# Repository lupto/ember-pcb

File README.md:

# EMBER PCB

This is the PCB for interfacing the EMBER macro with FPGA, power supplies, probing, and power measurement.

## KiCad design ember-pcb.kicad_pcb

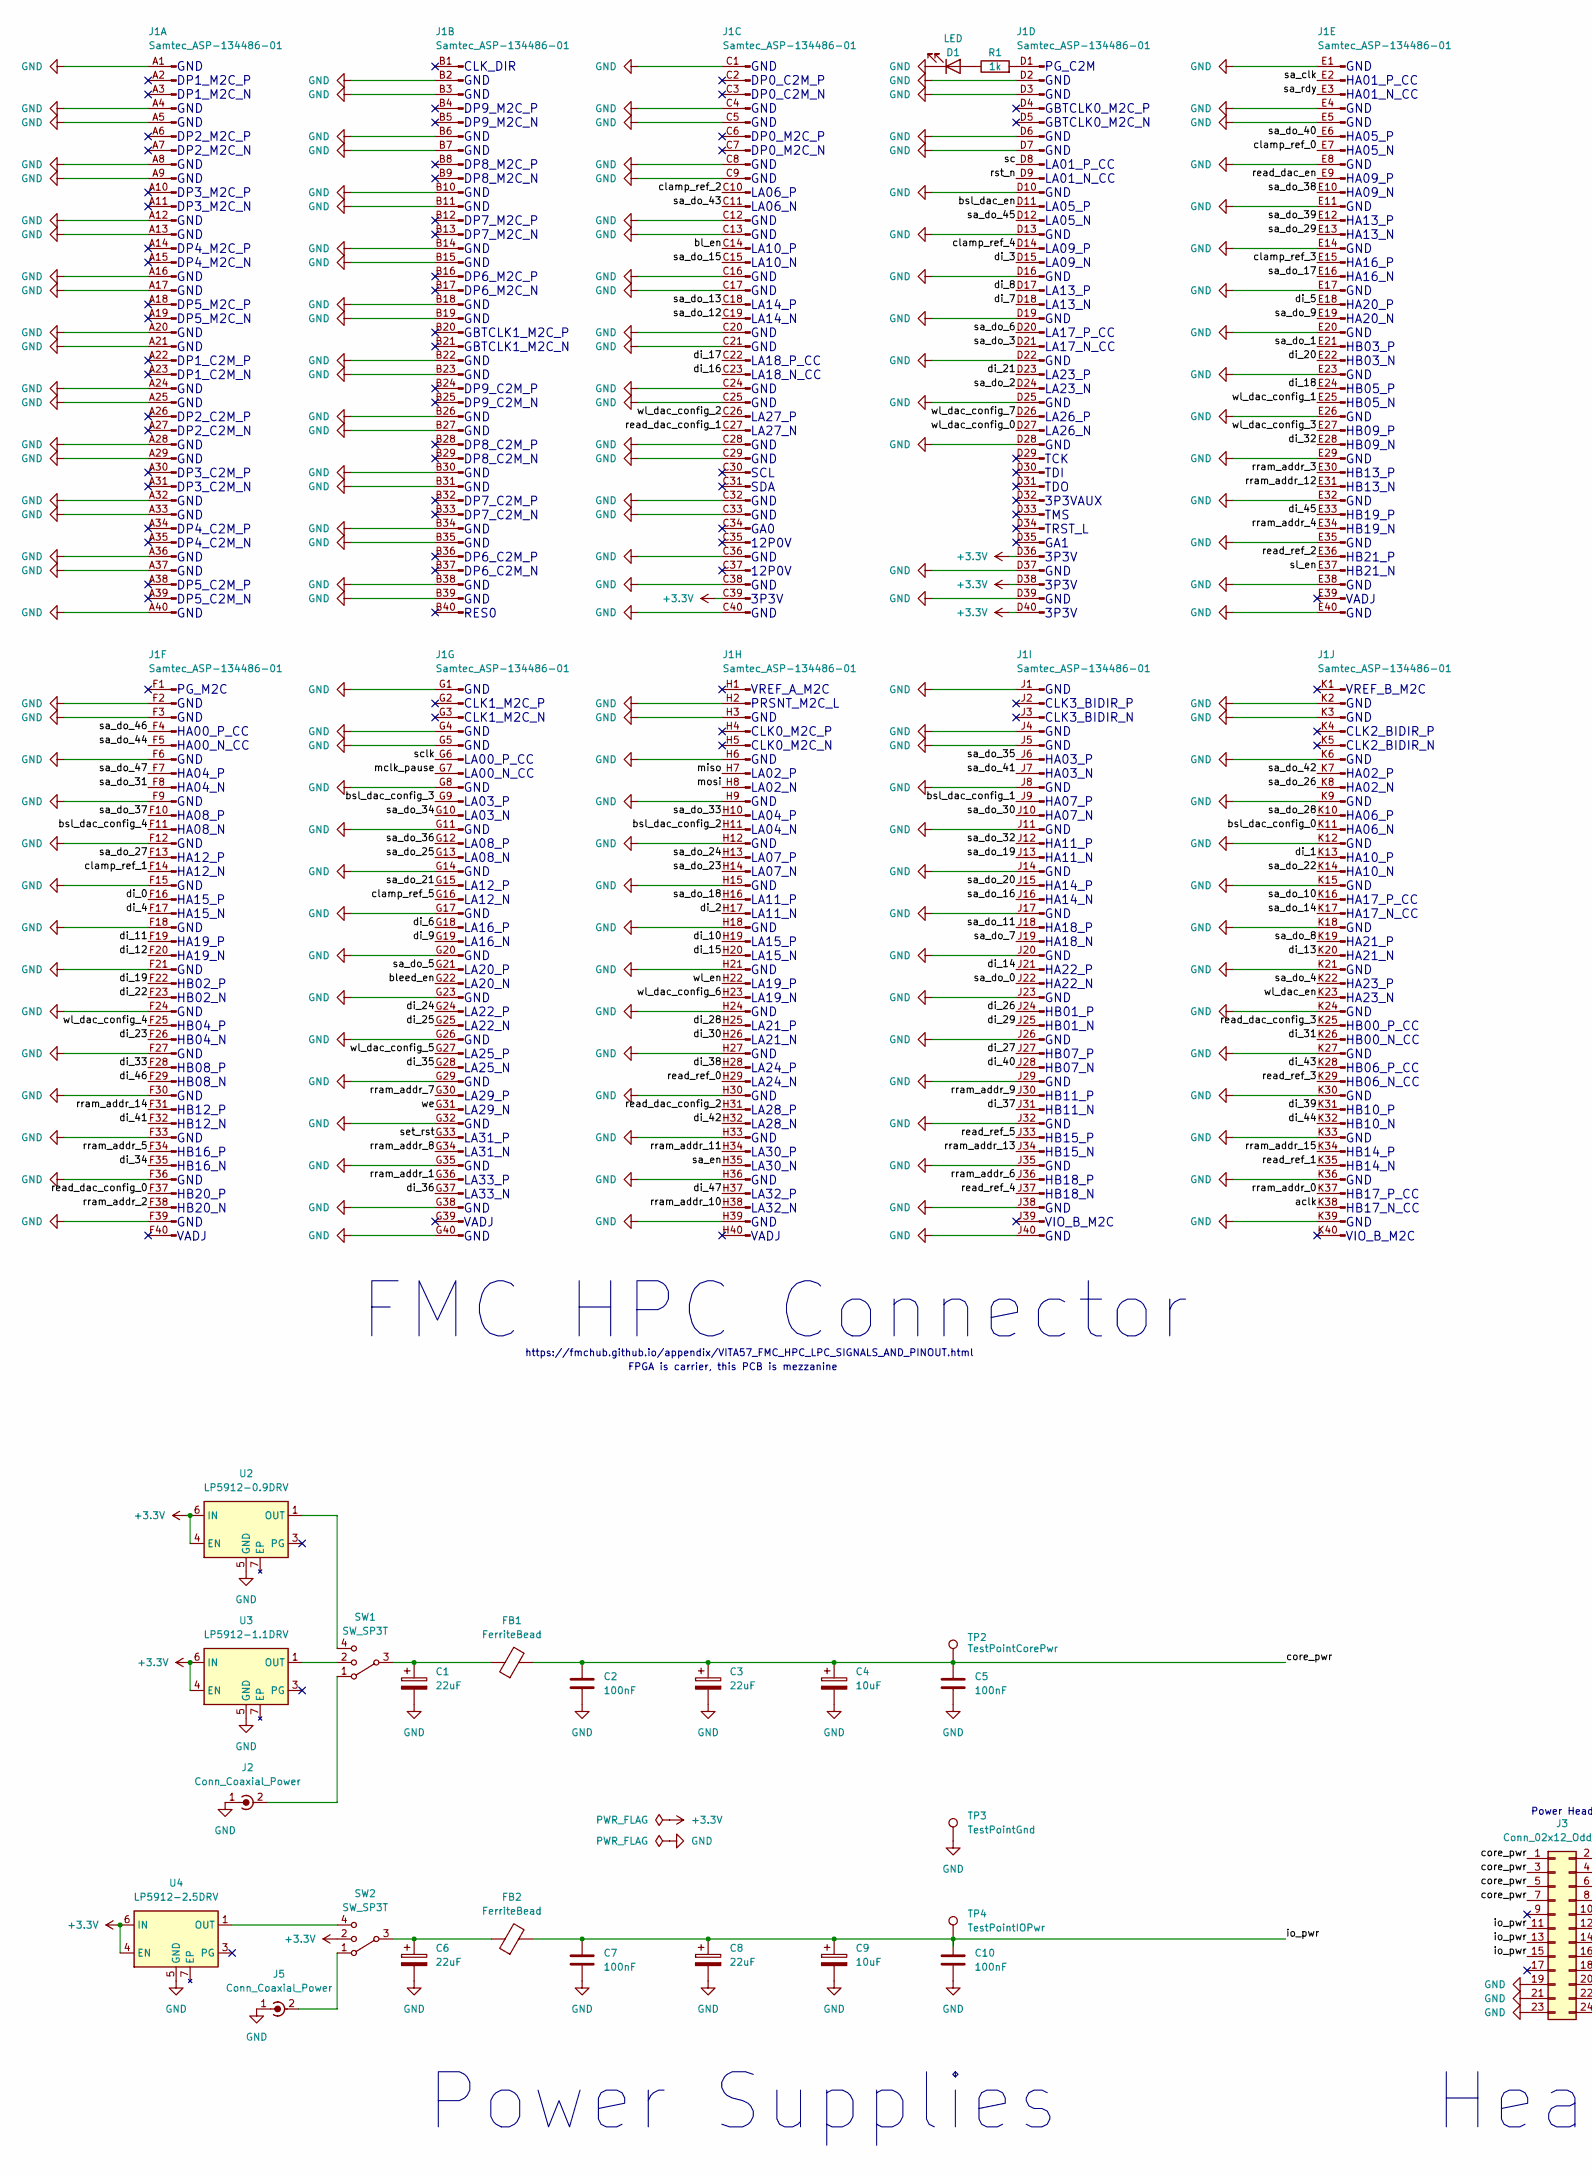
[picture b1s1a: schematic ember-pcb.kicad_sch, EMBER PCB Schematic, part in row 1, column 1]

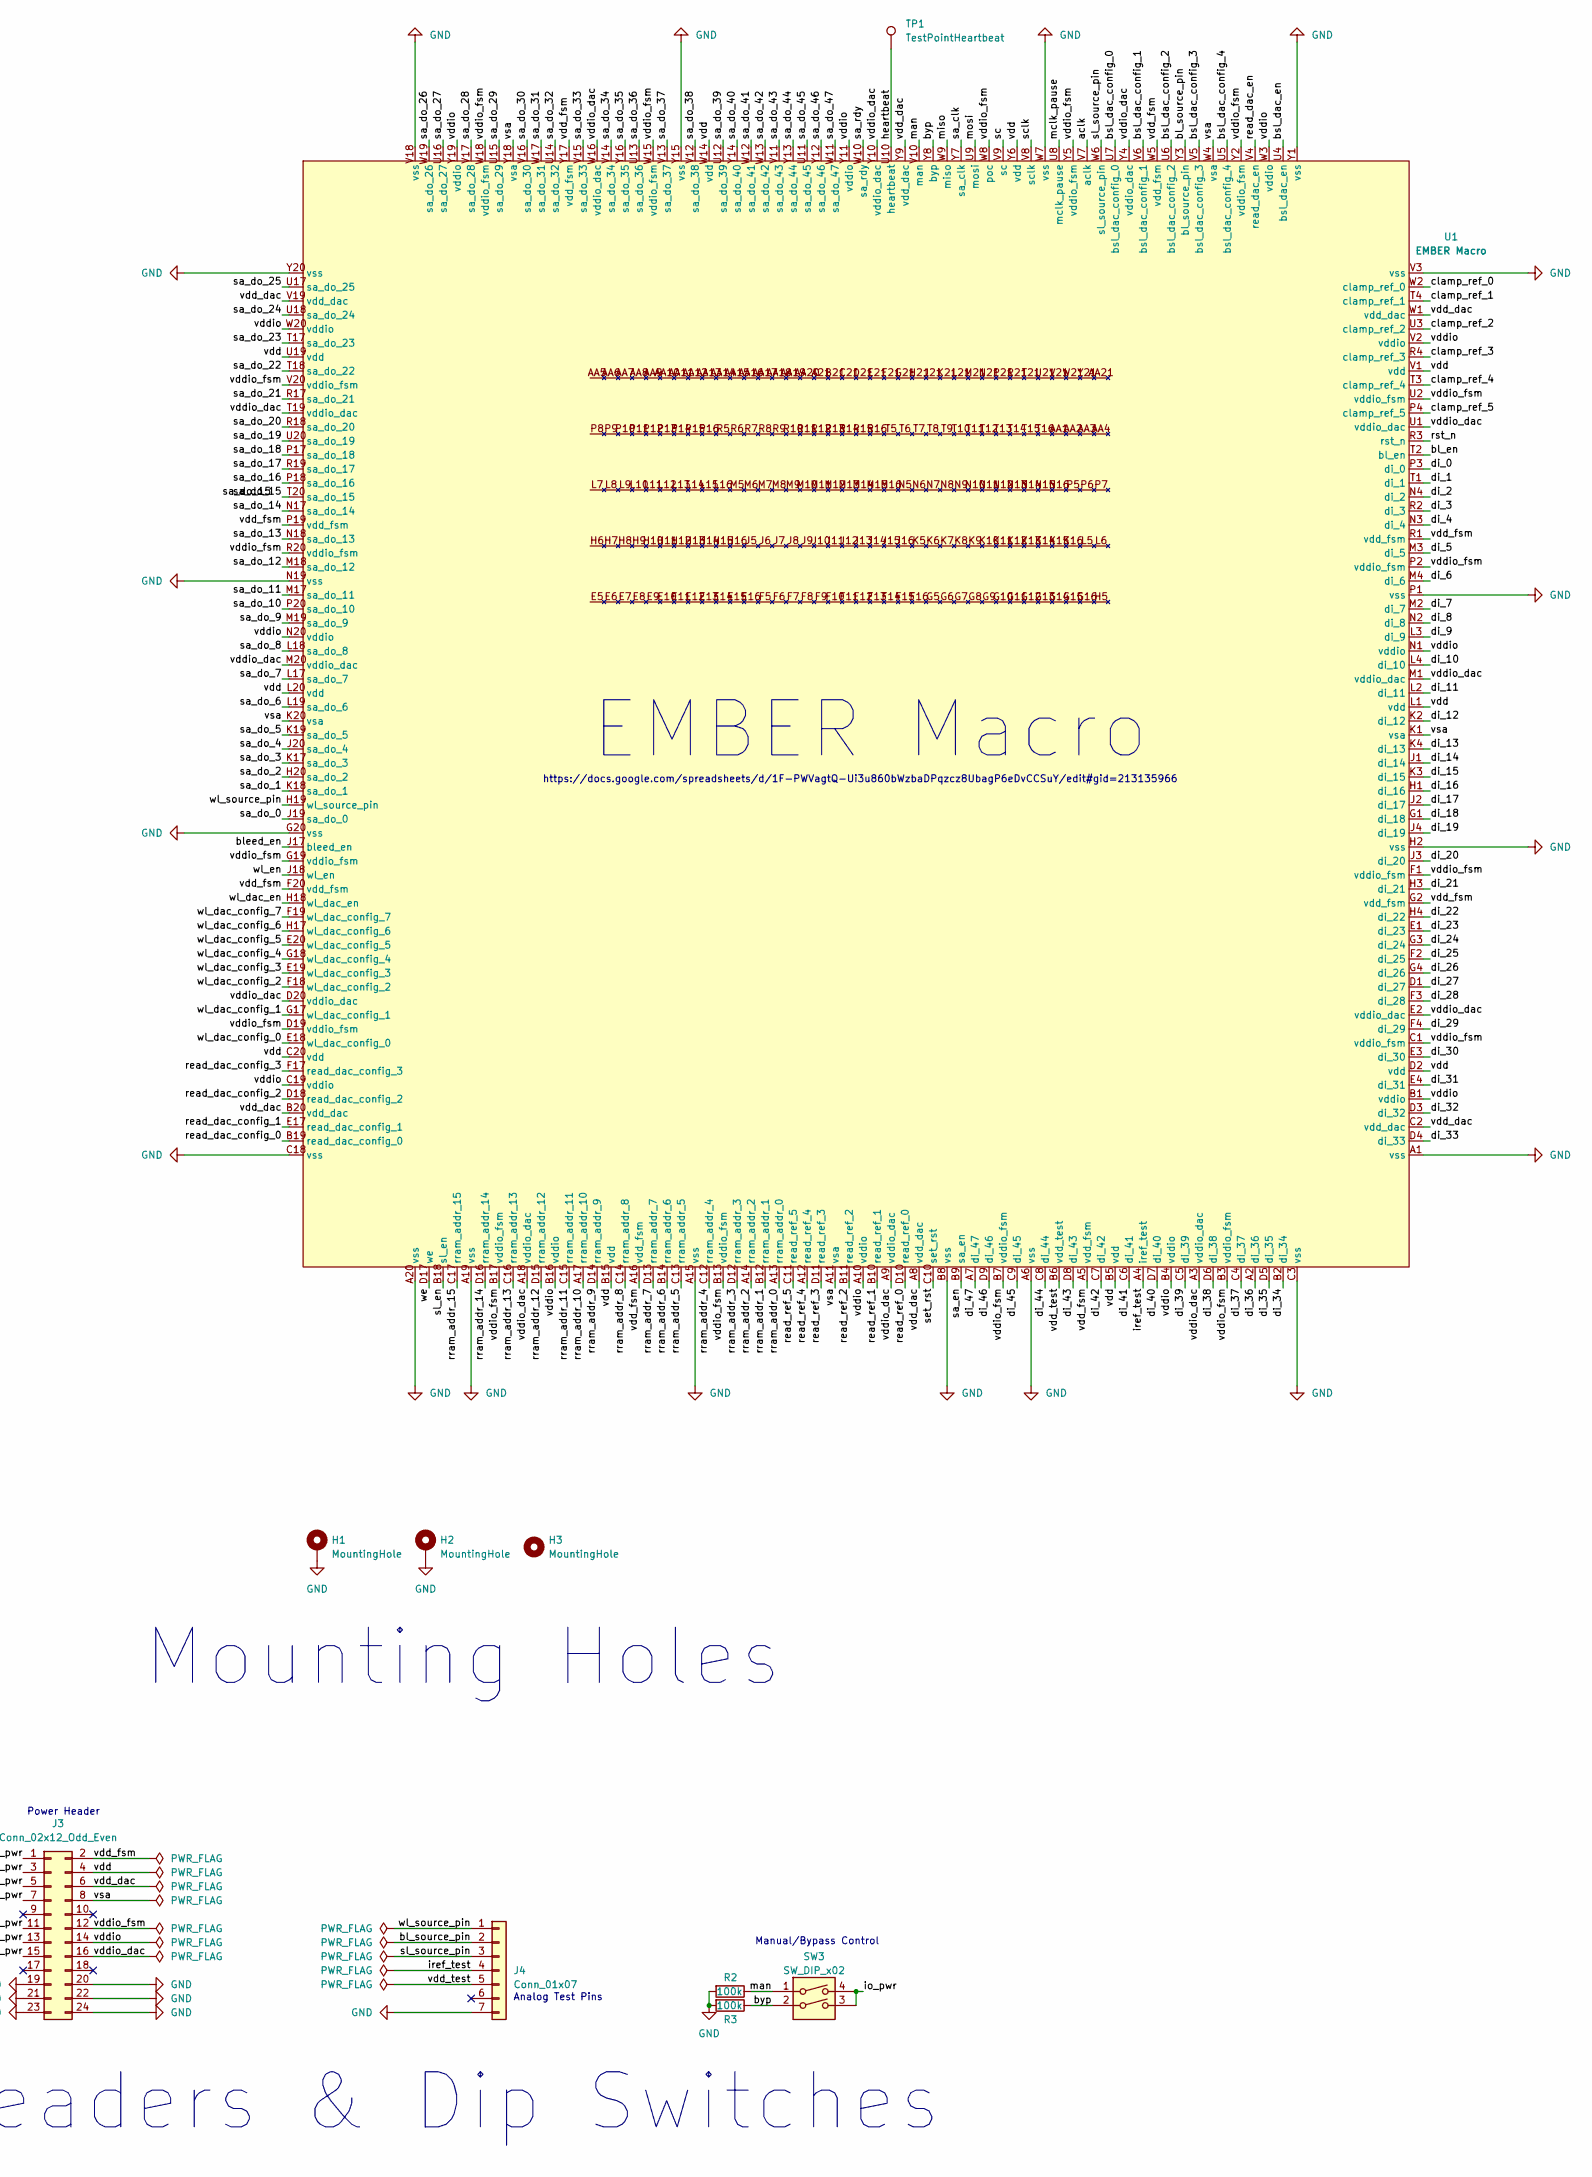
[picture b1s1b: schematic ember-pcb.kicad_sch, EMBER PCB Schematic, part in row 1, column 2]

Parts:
C1, C3, C6, C8: 22uF; CP_Elec_3x5.3
C2, C5, C7, C10: 100nF; CP_Elec_3x5.3
C4, C9: 10uF; CP_Elec_3x5.3
D1: LED; LED_0603_1608Metric
FB1, FB2: FerriteBead; LairdTech_28C0236-0JW-10
H1, H2: MountingHole; MountingHole_2.5mm_Pad
H3: MountingHole; MountingHole_2.5mm
J1: Samtec_ASP-134486-01; Samtec_FMC_ASP-134486-01_10x40_P1.27mm_Vertical
J2, J5: Conn_Coaxial_Power; SMA_Samtec_SMA-J-P-X-ST-EM1_EdgeMount
J3: Conn_02x12_Odd_Even; PinHeader_2x12_P2.54mm_Vertical
J4: Conn_01x07; PinHeader_1x07_P2.54mm_Vertical
R1: 1k; R_0603_1608Metric
R2, R3: 100k; R_0603_1608Metric
SW1, SW2: SW_SP3T; SW_SP3T_PCM13
SW3: SW_DIP_x02; SW_DIP_SPSTx02_Slide_Omron_A6S-210x_W8.9mm_P2.54mm
TP1: TestPointHeartbeat; TestPoint_Pad_D1.0mm
TP2: TestPointCorePwr; TestPoint_Pad_D1.0mm
TP3: TestPointGnd; TestPoint_Pad_D1.0mm
TP4: TestPointIOPwr; TestPoint_Pad_D1.0mm
U1: EMBER Macro; ZIF-441_Aries
U2: LP5912-0.9DRV; WSON-6-1EP_2x2mm_P0.65mm_EP1x1.6mm_ThermalVias
U3: LP5912-1.1DRV; WSON-6-1EP_2x2mm_P0.65mm_EP1x1.6mm_ThermalVias
U4: LP5912-2.5DRV; WSON-6-1EP_2x2mm_P0.65mm_EP1x1.6mm_ThermalVias

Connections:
+3.3V: J1.C39 (Pin_39), J1.D36 (Pin_36), J1.D38 (Pin_38), J1.D40 (Pin_40), SW2.2, U2.4 (EN), U2.6 (IN), U3.4 (EN), U3.6 (IN), U4.4 (EN), U4.6 (IN)
/aclk: J1.K38 (Pin_38), U1.V7 (aclk)
/bl_en: J1.C14 (Pin_14), U1.T2 (bl_en)
/bl_source_pin: J4.2, U1.Y3 (bl_source_pin)
/bleed_en: J1.G22 (Pin_22), U1.J17 (bleed_en)
/bsl_dac_config_0: J1.K11 (Pin_11), U1.U7 (bsl_dac_config_0)
/bsl_dac_config_1: J1.J9 (Pin_9), U1.V6 (bsl_dac_config_1)
/bsl_dac_config_2: J1.H11 (Pin_11), U1.U6 (bsl_dac_config_2)
/bsl_dac_config_3: J1.G9 (Pin_9), U1.V5 (bsl_dac_config_3)
/bsl_dac_config_4: J1.F11 (Pin_11), U1.U5 (bsl_dac_config_4)
/bsl_dac_en: J1.D11 (Pin_11), U1.U4 (bsl_dac_en)
/byp: R3.1, SW3.2, U1.Y8 (byp)
/clamp_ref_0: J1.E7 (Pin_7), U1.W2 (clamp_ref_0)
/clamp_ref_1: J1.F14 (Pin_14), U1.T4 (clamp_ref_1)
/clamp_ref_2: J1.C10 (Pin_10), U1.U3 (clamp_ref_2)
/clamp_ref_3: J1.E15 (Pin_15), U1.R4 (clamp_ref_3)
/clamp_ref_4: J1.D14 (Pin_14), U1.T3 (clamp_ref_4)
/clamp_ref_5: J1.G16 (Pin_16), U1.P4 (clamp_ref_5)
/core_pwr: C2.1, C3.1, C4.1, C5.1, FB1.2, J3.1, J3.3, J3.5, J3.7, TP2.1
/di_0: J1.F16 (Pin_16), U1.P3 (di_0)
/di_1: J1.K13 (Pin_13), U1.T1 (di_1)
/di_2: J1.H17 (Pin_17), U1.N4 (di_2)
/di_3: J1.D15 (Pin_15), U1.R2 (di_3)
/di_4: J1.F17 (Pin_17), U1.N3 (di_4)
/di_5: J1.E18 (Pin_18), U1.M3 (di_5)
/di_6: J1.G18 (Pin_18), U1.M4 (di_6)
/di_7: J1.D18 (Pin_18), U1.M2 (di_7)
/di_8: J1.D17 (Pin_17), U1.N2 (di_8)
/di_9: J1.G19 (Pin_19), U1.L3 (di_9)
/di_10: J1.H19 (Pin_19), U1.L4 (di_10)
/di_11: J1.F19 (Pin_19), U1.L2 (di_11)
/di_12: J1.F20 (Pin_20), U1.K2 (di_12)
/di_13: J1.K20 (Pin_20), U1.K4 (di_13)
/di_14: J1.J21 (Pin_21), U1.J1 (di_14)
/di_15: J1.H20 (Pin_20), U1.K3 (di_15)
/di_16: J1.C23 (Pin_23), U1.H1 (di_16)
/di_17: J1.C22 (Pin_22), U1.J2 (di_17)
/di_18: J1.E24 (Pin_24), U1.G1 (di_18)
/di_19: J1.F22 (Pin_22), U1.J4 (di_19)
/di_20: J1.E22 (Pin_22), U1.J3 (di_20)
/di_21: J1.D23 (Pin_23), U1.H3 (di_21)
/di_22: J1.F23 (Pin_23), U1.H4 (di_22)
/di_23: J1.F26 (Pin_26), U1.E1 (di_23)
/di_24: J1.G24 (Pin_24), U1.G3 (di_24)
/di_25: J1.G25 (Pin_25), U1.F2 (di_25)
/di_26: J1.J24 (Pin_24), U1.G4 (di_26)
/di_27: J1.J27 (Pin_27), U1.D1 (di_27)
/di_28: J1.H25 (Pin_25), U1.F3 (di_28)
/di_29: J1.J25 (Pin_25), U1.F4 (di_29)
/di_30: J1.H26 (Pin_26), U1.E3 (di_30)
/di_31: J1.K26 (Pin_26), U1.E4 (di_31)
/di_32: J1.E28 (Pin_28), U1.D3 (di_32)
/di_33: J1.F28 (Pin_28), U1.D4 (di_33)
/di_34: J1.F35 (Pin_35), U1.B2 (di_34)
/di_35: J1.G28 (Pin_28), U1.D5 (di_35)
/di_36: J1.G37 (Pin_37), U1.A2 (di_36)
/di_37: J1.J31 (Pin_31), U1.C4 (di_37)
/di_38: J1.H28 (Pin_28), U1.D6 (di_38)
/di_39: J1.K31 (Pin_31), U1.C5 (di_39)
/di_40: J1.J28 (Pin_28), U1.D7 (di_40)
/di_41: J1.F32 (Pin_32), U1.C6 (di_41)
/di_42: J1.H32 (Pin_32), U1.C7 (di_42)
/di_43: J1.K28 (Pin_28), U1.D8 (di_43)
/di_44: J1.K32 (Pin_32), U1.C8 (di_44)
/di_45: J1.E33 (Pin_33), U1.C9 (di_45)
/di_46: J1.F29 (Pin_29), U1.D9 (di_46)
/di_47: J1.H37 (Pin_37), U1.A7 (di_47)
/heartbeat: TP1.1, U1.U10 (heartbeat)
/io_pwr: C7.1, C8.1, C9.1, C10.1, FB2.2, J3.11, J3.13, J3.15, SW3.3, SW3.4, TP4.1
/iref_test: J4.4, U1.A4 (iref_test)
/man: R2.1, SW3.1, U1.V10 (man)
/mclk_pause: J1.G7 (Pin_7), U1.U8 (mclk_pause)
/miso: J1.H7 (Pin_7), U1.W9 (miso)
/mosi: J1.H8 (Pin_8), U1.U9 (mosi)
/read_dac_config_0: J1.F37 (Pin_37), U1.B19 (read_dac_config_0)
/read_dac_config_1: J1.C27 (Pin_27), U1.E17 (read_dac_config_1)
/read_dac_config_2: J1.H31 (Pin_31), U1.D18 (read_dac_config_2)
/read_dac_config_3: J1.K25 (Pin_25), U1.F17 (read_dac_config_3)
/read_dac_en: J1.E9 (Pin_9), U1.V4 (read_dac_en)
/read_ref_0: J1.H29 (Pin_29), U1.D10 (read_ref_0)
/read_ref_1: J1.K35 (Pin_35), U1.B10 (read_ref_1)
/read_ref_2: J1.E36 (Pin_36), U1.B11 (read_ref_2)
/read_ref_3: J1.K29 (Pin_29), U1.D11 (read_ref_3)
/read_ref_4: J1.J37 (Pin_37), U1.A12 (read_ref_4)
/read_ref_5: J1.J33 (Pin_33), U1.C11 (read_ref_5)
/rram_addr_0: J1.K37 (Pin_37), U1.A13 (rram_addr_0)
/rram_addr_1: J1.G36 (Pin_36), U1.B12 (rram_addr_1)
/rram_addr_2: J1.F38 (Pin_38), U1.A14 (rram_addr_2)
/rram_addr_3: J1.E30 (Pin_30), U1.D12 (rram_addr_3)
/rram_addr_4: J1.E34 (Pin_34), U1.C12 (rram_addr_4)
/rram_addr_5: J1.F34 (Pin_34), U1.C13 (rram_addr_5)
/rram_addr_6: J1.J36 (Pin_36), U1.B14 (rram_addr_6)
/rram_addr_7: J1.G30 (Pin_30), U1.D13 (rram_addr_7)
/rram_addr_8: J1.G34 (Pin_34), U1.C14 (rram_addr_8)
/rram_addr_9: J1.J30 (Pin_30), U1.D14 (rram_addr_9)
/rram_addr_10: J1.H38 (Pin_38), U1.A17 (rram_addr_10)
/rram_addr_11: J1.H34 (Pin_34), U1.C15 (rram_addr_11)
/rram_addr_12: J1.E31 (Pin_31), U1.D15 (rram_addr_12)
/rram_addr_13: J1.J34 (Pin_34), U1.C16 (rram_addr_13)
/rram_addr_14: J1.F31 (Pin_31), U1.D16 (rram_addr_14)
/rram_addr_15: J1.K34 (Pin_34), U1.C17 (rram_addr_15)
/rst_n: J1.D9 (Pin_9), U1.R3 (rst_n)
/sa_clk: J1.E2 (Pin_2), U1.Y7 (sa_clk)
/sa_do_0: J1.J22 (Pin_22), U1.J19 (sa_do_0)
/sa_do_1: J1.E21 (Pin_21), U1.K18 (sa_do_1)
/sa_do_2: J1.D24 (Pin_24), U1.H20 (sa_do_2)
/sa_do_3: J1.D21 (Pin_21), U1.K17 (sa_do_3)
/sa_do_4: J1.K22 (Pin_22), U1.J20 (sa_do_4)
/sa_do_5: J1.G21 (Pin_21), U1.K19 (sa_do_5)
/sa_do_6: J1.D20 (Pin_20), U1.L19 (sa_do_6)
/sa_do_7: J1.J19 (Pin_19), U1.L17 (sa_do_7)
/sa_do_8: J1.K19 (Pin_19), U1.L18 (sa_do_8)
/sa_do_9: J1.E19 (Pin_19), U1.M19 (sa_do_9)
/sa_do_10: J1.K16 (Pin_16), U1.P20 (sa_do_10)
/sa_do_11: J1.J18 (Pin_18), U1.M17 (sa_do_11)
/sa_do_12: J1.C19 (Pin_19), U1.M18 (sa_do_12)
/sa_do_13: J1.C18 (Pin_18), U1.N18 (sa_do_13)
/sa_do_14: J1.K17 (Pin_17), U1.N17 (sa_do_14)
/sa_do_15: J1.C15 (Pin_15), U1.T20 (sa_do_15)
/sa_do_16: J1.J16 (Pin_16), U1.P18 (sa_do_16)
/sa_do_17: J1.E16 (Pin_16), U1.R19 (sa_do_17)
/sa_do_18: J1.H16 (Pin_16), U1.P17 (sa_do_18)
/sa_do_19: J1.J13 (Pin_13), U1.U20 (sa_do_19)
/sa_do_20: J1.J15 (Pin_15), U1.R18 (sa_do_20)
/sa_do_21: J1.G15 (Pin_15), U1.R17 (sa_do_21)
/sa_do_22: J1.K14 (Pin_14), U1.T18 (sa_do_22)
/sa_do_23: J1.H14 (Pin_14), U1.T17 (sa_do_23)
/sa_do_24: J1.H13 (Pin_13), U1.U18 (sa_do_24)
/sa_do_25: J1.G13 (Pin_13), U1.U17 (sa_do_25)
/sa_do_26: J1.K8 (Pin_8), U1.W19 (sa_do_26)
/sa_do_27: J1.F13 (Pin_13), U1.U16 (sa_do_27)
/sa_do_28: J1.K10 (Pin_10), U1.V17 (sa_do_28)
/sa_do_29: J1.E13 (Pin_13), U1.U15 (sa_do_29)
/sa_do_30: J1.J10 (Pin_10), U1.V16 (sa_do_30)
/sa_do_31: J1.F8 (Pin_8), U1.W17 (sa_do_31)
/sa_do_32: J1.J12 (Pin_12), U1.U14 (sa_do_32)
/sa_do_33: J1.H10 (Pin_10), U1.V15 (sa_do_33)
/sa_do_34: J1.G10 (Pin_10), U1.V14 (sa_do_34)
/sa_do_35: J1.J6 (Pin_6), U1.Y16 (sa_do_35)
/sa_do_36: J1.G12 (Pin_12), U1.U13 (sa_do_36)
/sa_do_37: J1.F10 (Pin_10), U1.V13 (sa_do_37)
/sa_do_38: J1.E10 (Pin_10), U1.V12 (sa_do_38)
/sa_do_39: J1.E12 (Pin_12), U1.U12 (sa_do_39)
/sa_do_40: J1.E6 (Pin_6), U1.Y14 (sa_do_40)
/sa_do_41: J1.J7 (Pin_7), U1.W12 (sa_do_41)
/sa_do_42: J1.K7 (Pin_7), U1.W13 (sa_do_42)
/sa_do_43: J1.C11 (Pin_11), U1.V11 (sa_do_43)
/sa_do_44: J1.F5 (Pin_5), U1.Y13 (sa_do_44)
/sa_do_45: J1.D12 (Pin_12), U1.U11 (sa_do_45)
/sa_do_46: J1.F4 (Pin_4), U1.Y12 (sa_do_46)
/sa_do_47: J1.F7 (Pin_7), U1.W11 (sa_do_47)
/sa_en: J1.H35 (Pin_35), U1.B9 (sa_en)
/sa_rdy: J1.E3 (Pin_3), U1.W10 (sa_rdy)
/sc: J1.D8 (Pin_8), U1.V9 (sc)
/sclk: J1.G6 (Pin_6), U1.V8 (sclk)
/set_rst: J1.G33 (Pin_33), U1.C10 (set_rst)
/sl_en: J1.E37 (Pin_37), U1.B18 (sl_en)
/sl_source_pin: J4.3, U1.W6 (sl_source_pin)
/vdd: J3.4, U1.B5 (vdd), U1.B15 (vdd), U1.C20 (vdd), U1.D2 (vdd), U1.L1 (vdd), U1.L20 (vdd), U1.U19 (vdd), U1.V1 (vdd), U1.W14 (vdd), U1.Y6 (vdd)
/vdd_dac: J3.6, U1.A8 (vdd_dac), U1.B20 (vdd_dac), U1.C2 (vdd_dac), U1.V19 (vdd_dac), U1.W1 (vdd_dac), U1.Y9 (vdd_dac)
/vdd_fsm: J3.2, U1.A5 (vdd_fsm), U1.A16 (vdd_fsm), U1.F20 (vdd_fsm), U1.G2 (vdd_fsm), U1.P19 (vdd_fsm), U1.R1 (vdd_fsm), U1.W5 (vdd_fsm), U1.Y17 (vdd_fsm)
/vdd_test: J4.5, U1.B6 (vdd_test)
/vddio: J3.14, U1.A10 (vddio), U1.B1 (vddio), U1.B4 (vddio), U1.B16 (vddio), U1.C19 (vddio), U1.N1 (vddio), U1.N20 (vddio), U1.V2 (vddio), U1.W3 (vddio), U1.W20 (vddio), U1.Y11 (vddio), U1.Y19 (vddio)
/vddio_dac: J3.16, U1.A3 (vddio_dac), U1.A9 (vddio_dac), U1.A18 (vddio_dac), U1.D20 (vddio_dac), U1.E2 (vddio_dac), U1.M1 (vddio_dac), U1.M20 (vddio_dac), U1.T19 (vddio_dac), U1.U1 (vddio_dac), U1.W16 (vddio_dac), U1.Y4 (vddio_dac), U1.Y10 (vddio_dac)
/vddio_fsm: J3.12, U1.B3 (vddio_fsm), U1.B7 (vddio_fsm), U1.B13 (vddio_fsm), U1.B17 (vddio_fsm), U1.C1 (vddio_fsm), U1.D19 (vddio_fsm), U1.F1 (vddio_fsm), U1.G19 (vddio_fsm), U1.P2 (vddio_fsm), U1.R20 (vddio_fsm), U1.U2 (vddio_fsm), U1.V20 (vddio_fsm), U1.W8 (poc), U1.W15 (vddio_fsm), U1.W18 (vddio_fsm), U1.Y2 (vddio_fsm), U1.Y5 (vddio_fsm)
/vsa: J3.8, U1.A11 (vsa), U1.K1 (vsa), U1.K20 (vsa), U1.W4 (vsa), U1.Y18 (vsa)
/we: J1.G31 (Pin_31), U1.D17 (we)
/wl_dac_config_0: J1.D27 (Pin_27), U1.E18 (wl_dac_config_0)
/wl_dac_config_1: J1.E25 (Pin_25), U1.G17 (wl_dac_config_1)
/wl_dac_config_2: J1.C26 (Pin_26), U1.F18 (wl_dac_config_2)
/wl_dac_config_3: J1.E27 (Pin_27), U1.E19 (wl_dac_config_3)
/wl_dac_config_4: J1.F25 (Pin_25), U1.G18 (wl_dac_config_4)
/wl_dac_config_5: J1.G27 (Pin_27), U1.E20 (wl_dac_config_5)
/wl_dac_config_6: J1.H23 (Pin_23), U1.H17 (wl_dac_config_6)
/wl_dac_config_7: J1.D26 (Pin_26), U1.F19 (wl_dac_config_7)
/wl_dac_en: J1.K23 (Pin_23), U1.H18 (wl_dac_en)
/wl_en: J1.H22 (Pin_22), U1.J18 (wl_en)
/wl_source_pin: J4.1, U1.H19 (wl_source_pin)
GND: C1.2, C2.2, C3.2, C4.2, C5.2, C6.2, C7.2, C8.2, C9.2, C10.2, D1.1 (K), H1.1, H2.1, J1.A1 (Pin_1), J1.A4 (Pin_4), J1.A5 (Pin_5), J1.A8 (Pin_8), J1.A9 (Pin_9), J1.A12 (Pin_12), J1.A13 (Pin_13), J1.A16 (Pin_16), J1.A17 (Pin_17), J1.A20 (Pin_20), J1.A21 (Pin_21), J1.A24 (Pin_24), J1.A25 (Pin_25), J1.A28 (Pin_28), J1.A29 (Pin_29), J1.A32 (Pin_32), J1.A33 (Pin_33), J1.A36 (Pin_36), J1.A37 (Pin_37), J1.A40 (Pin_40), J1.B2 (Pin_2), J1.B3 (Pin_3), J1.B6 (Pin_6), J1.B7 (Pin_7), J1.B10 (Pin_10), J1.B11 (Pin_11), J1.B14 (Pin_14), J1.B15 (Pin_15), J1.B18 (Pin_18), J1.B19 (Pin_19), J1.B22 (Pin_22), J1.B23 (Pin_23), J1.B26 (Pin_26), J1.B27 (Pin_27), J1.B30 (Pin_30), J1.B31 (Pin_31), J1.B34 (Pin_34), J1.B35 (Pin_35), J1.B38 (Pin_38), J1.B39 (Pin_39), J1.C1 (Pin_1), J1.C4 (Pin_4), J1.C5 (Pin_5), J1.C8 (Pin_8), J1.C9 (Pin_9), J1.C12 (Pin_12), J1.C13 (Pin_13), J1.C16 (Pin_16), J1.C17 (Pin_17), J1.C20 (Pin_20), J1.C21 (Pin_21), J1.C24 (Pin_24), J1.C25 (Pin_25), J1.C28 (Pin_28), J1.C29 (Pin_29), J1.C32 (Pin_32), J1.C33 (Pin_33), J1.C36 (Pin_36), J1.C38 (Pin_38), J1.C40 (Pin_40), J1.D2 (Pin_2), J1.D3 (Pin_3), J1.D6 (Pin_6), J1.D7 (Pin_7), J1.D10 (Pin_10), J1.D13 (Pin_13), J1.D16 (Pin_16), J1.D19 (Pin_19), J1.D22 (Pin_22), J1.D25 (Pin_25), J1.D28 (Pin_28), J1.D37 (Pin_37), J1.D39 (Pin_39), J1.E1 (Pin_1), J1.E4 (Pin_4), J1.E5 (Pin_5), J1.E8 (Pin_8), J1.E11 (Pin_11), J1.E14 (Pin_14), J1.E17 (Pin_17), J1.E20 (Pin_20), J1.E23 (Pin_23), J1.E26 (Pin_26), J1.E29 (Pin_29), J1.E32 (Pin_32), J1.E35 (Pin_35), J1.E38 (Pin_38), J1.E40 (Pin_40), J1.F2 (Pin_2), J1.F3 (Pin_3), J1.F6 (Pin_6), J1.F9 (Pin_9), J1.F12 (Pin_12), J1.F15 (Pin_15), J1.F18 (Pin_18), J1.F21 (Pin_21), J1.F24 (Pin_24), J1.F27 (Pin_27), J1.F30 (Pin_30), J1.F33 (Pin_33), J1.F36 (Pin_36), J1.F39 (Pin_39), J1.G1 (Pin_1), J1.G4 (Pin_4), J1.G5 (Pin_5), J1.G8 (Pin_8), J1.G11 (Pin_11), J1.G14 (Pin_14), J1.G17 (Pin_17), J1.G20 (Pin_20), J1.G23 (Pin_23), J1.G26 (Pin_26), J1.G29 (Pin_29), J1.G32 (Pin_32), J1.G35 (Pin_35), J1.G38 (Pin_38), J1.G40 (Pin_40), J1.H2 (Pin_2), J1.H3 (Pin_3), J1.H6 (Pin_6), J1.H9 (Pin_9), J1.H12 (Pin_12), J1.H15 (Pin_15), J1.H18 (Pin_18), J1.H21 (Pin_21), J1.H24 (Pin_24), J1.H27 (Pin_27), J1.H30 (Pin_30), J1.H33 (Pin_33), J1.H36 (Pin_36), J1.H39 (Pin_39), J1.J1 (Pin_1), J1.J4 (Pin_4), J1.J5 (Pin_5), J1.J8 (Pin_8), J1.J11 (Pin_11), J1.J14 (Pin_14), J1.J17 (Pin_17), J1.J20 (Pin_20), J1.J23 (Pin_23), J1.J26 (Pin_26), J1.J29 (Pin_29), J1.J32 (Pin_32), J1.J35 (Pin_35), J1.J38 (Pin_38), J1.J40 (Pin_40), J1.K2 (Pin_2), J1.K3 (Pin_3), J1.K6 (Pin_6), J1.K9 (Pin_9), J1.K12 (Pin_12), J1.K15 (Pin_15), J1.K18 (Pin_18), J1.K21 (Pin_21), J1.K24 (Pin_24), J1.K27 (Pin_27), J1.K30 (Pin_30), J1.K33 (Pin_33), J1.K36 (Pin_36), J1.K39 (Pin_39), J2.1 (In), J3.19, J3.20, J3.21, J3.22, J3.23, J3.24, J4.7, J5.1 (In), R2.2, R3.2, TP3.1, U1.A1 (vss), U1.A6 (vss), U1.A15 (vss), U1.A19 (vss), U1.A20 (vss), U1.B8 (vss), U1.C3 (vss), U1.C18 (vss), U1.G20 (vss), U1.H2 (vss), U1.N19 (vss), U1.P1 (vss), U1.V3 (vss), U1.V18 (vss), U1.W7 (vss), U1.Y1 (vss), U1.Y15 (vss), U1.Y20 (vss), U2.5 (GND), U3.5 (GND), U4.5 (GND)
unnamed: C1.1, FB1.1, SW1.3
unnamed: C6.1, FB2.1, SW2.3
unnamed: D1.2 (A), R1.1
unnamed: J1.D1 (Pin_1), R1.2
unnamed: J2.2 (Ext), SW1.1
unnamed: J5.2 (Ext), SW2.1
unnamed: SW1.2, U3.1 (OUT)
unnamed: SW1.4, U2.1 (OUT)
unnamed: SW2.4, U4.1 (OUT)

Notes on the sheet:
Manual/Bypass Control
VREF_B_M2C GND GND CLK2_BIDIR_P CLK2_BIDIR_N GND HA02_P HA02_N GND HA06_P HA06_N GND HA10_P HA10_N GND HA17_P_CC HA17_N_CC GND HA21_P HA21_N GND HA23_P HA23_N GND HB00_P_CC HB00_N_CC GND HB06_P_CC HB06_N_CC GND HB10_P HB10_N GND HB14_P HB14_N GND HB17_P_CC HB17_N_CC GND VIO_B_M2C
https://fmchub.github.io/appendix/VITA57_FMC_HPC_LPC_SIGNALS_AND_PINOUT.html
GND DP1_M2C_P DP1_M2C_N GND GND DP2_M2C_P DP2_M2C_N GND GND DP3_M2C_P DP3_M2C_N GND GND DP4_M2C_P DP4_M2C_N GND GND DP5_M2C_P DP5_M2C_N GND GND DP1_C2M_P DP1_C2M_N GND GND DP2_C2M_P DP2_C2M_N GND GND DP3_C2M_P DP3_C2M_N GND GND DP4_C2M_P DP4_C2M_N GND GND DP5_C2M_P DP5_C2M_N GND
VREF_A_M2C PRSNT_M2C_L GND CLK0_M2C_P CLK0_M2C_N GND LA02_P LA02_N GND LA04_P LA04_N GND LA07_P LA07_N GND LA11_P LA11_N GND LA15_P LA15_N GND LA19_P LA19_N GND LA21_P LA21_N GND LA24_P LA24_N GND LA28_P LA28_N GND LA30_P LA30_N GND LA32_P LA32_N GND VADJ
PG_M2C GND GND HA00_P_CC HA00_N_CC GND HA04_P HA04_N GND HA08_P HA08_N GND HA12_P HA12_N GND HA15_P HA15_N GND HA19_P HA19_N GND HB02_P HB02_N GND HB04_P HB04_N GND HB08_P HB08_N GND HB12_P HB12_N GND HB16_P HB16_N GND HB20_P HB20_N GND VADJ
https://docs.google.com/spreadsheets/d/1F-PWVagtQ-Ui3u860bWzbaDPqzcz8UbagP6eDvCCSuY/edit#gid=213135966
GND CLK3_BIDIR_P CLK3_BIDIR_N GND GND HA03_P HA03_N GND HA07_P HA07_N GND HA11_P HA11_N GND HA14_P HA14_N GND HA18_P HA18_N GND HA22_P HA22_N GND HB01_P HB01_N GND HB07_P HB07_N GND HB11_P HB11_N GND HB15_P HB15_N GND HB18_P HB18_N GND VIO_B_M2C GND
FMC HPC Connector
EMBER Macro
Mounting Holes
Power Supplies
Analog Test Pins
GND CLK1_M2C_P CLK1_M2C_N GND GND LA00_P_CC LA00_N_CC GND LA03_P LA03_N GND LA08_P LA08_N GND LA12_P LA12_N GND LA16_P LA16_N GND LA20_P LA20_N GND LA22_P LA22_N GND LA25_P LA25_N GND LA29_P LA29_N GND LA31_P LA31_N GND LA33_P LA33_N GND VADJ GND
FPGA is carrier, this PCB is mezzanine
GND HA01_P_CC HA01_N_CC GND GND HA05_P HA05_N GND HA09_P HA09_N GND HA13_P HA13_N GND HA16_P HA16_N GND HA20_P HA20_N GND HB03_P HB03_N GND HB05_P HB05_N GND HB09_P HB09_N GND HB13_P HB13_N GND HB19_P HB19_N GND HB21_P HB21_N GND VADJ GND
Power Header
PG_C2M GND GND GBTCLK0_M2C_P GBTCLK0_M2C_N GND GND LA01_P_CC LA01_N_CC GND LA05_P LA05_N GND LA09_P LA09_N GND LA13_P LA13_N GND LA17_P_CC LA17_N_CC GND LA23_P LA23_N GND LA26_P LA26_N GND TCK TDI TDO 3P3VAUX TMS TRST_L GA1 3P3V GND 3P3V GND 3P3V
CLK_DIR GND GND DP9_M2C_P DP9_M2C_N GND GND DP8_M2C_P DP8_M2C_N GND GND DP7_M2C_P DP7_M2C_N GND GND DP6_M2C_P DP6_M2C_N GND GND GBTCLK1_M2C_P GBTCLK1_M2C_N GND GND DP9_C2M_P DP9_C2M_N GND GND DP8_C2M_P DP8_C2M_N GND GND DP7_C2M_P DP7_C2M_N GND GND DP6_C2M_P DP6_C2M_N GND GND RES0
Headers & Dip Switches
GND DP0_C2M_P DP0_C2M_N GND GND DP0_M2C_P DP0_M2C_N GND GND LA06_P LA06_N GND GND LA10_P LA10_N GND GND LA14_P LA14_N GND GND LA18_P_CC LA18_N_CC GND GND LA27_P LA27_N GND GND SCL SDA GND GND GA0 12P0V GND 12P0V GND 3P3V GND

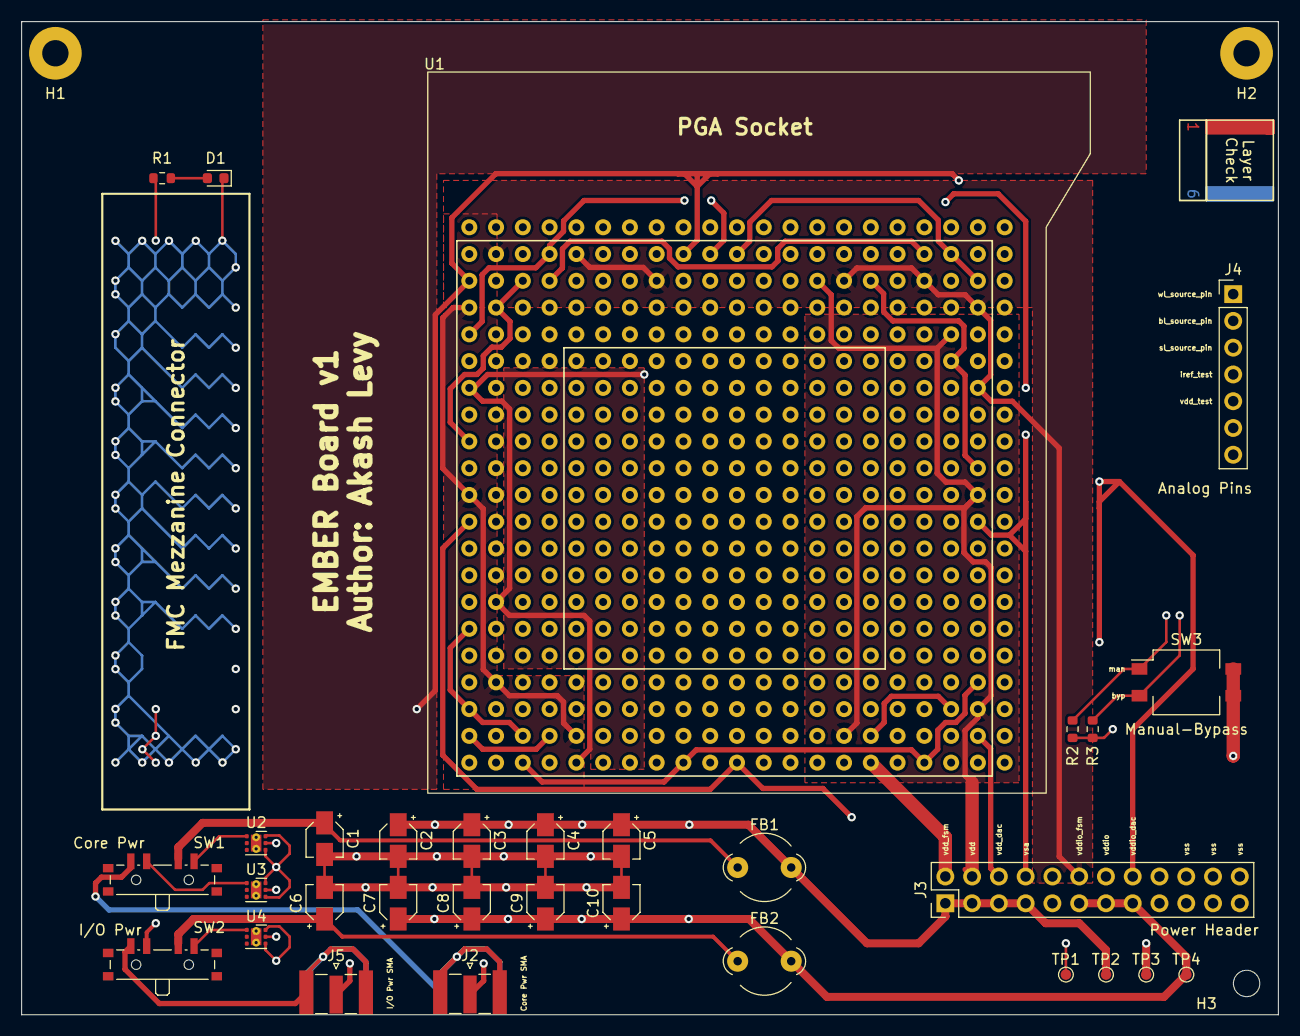
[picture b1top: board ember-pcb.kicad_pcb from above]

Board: 6 copper layers, 119.3 x 94.2 mm, 34 parts (0 on the bottom side), 27 nets.

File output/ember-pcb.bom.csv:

"Id";"Designator";"Package";"Quantity";"Designation";"Supplier and ref";
1;"J1";"Samtec_FMC_ASP-134486-01_10x40_P1.27mm_Vertical";1;"Samtec_ASP-134486-01";;;
2;"R2,R3";"R_0603_1608Metric";2;"100k";;;
3;"J3";"PinHeader_2x12_P2.54mm_Vertical";1;"Conn_02x12_Odd_Even";;;
4;"H3";"MountingHole_2.5mm";1;"MountingHole";;;
5;"SW2,SW1";"SW_SP3T_PCM13";2;"SW_SP3T";;;
6;"TP1";"TestPoint_Pad_D1.0mm";1;"TestPointHeartbeat";;;
7;"H1,H2";"MountingHole_2.5mm_Pad";2;"MountingHole";;;
8;"C8,C3,C1,C6";"CP_Elec_3x5.3";4;"22uF";;;
9;"TP2";"TestPoint_Pad_D1.0mm";1;"TestPointCorePwr";;;
10;"FB1,FB2";"LairdTech_28C0236-0JW-10";2;"FerriteBead";;;
11;"J4";"PinHeader_1x07_P2.54mm_Vertical";1;"Conn_01x07";;;
12;"J5,J2";"SMA_Samtec_SMA-J-P-X-ST-EM1_EdgeMount";2;"Conn_Coaxial_Power";;;
13;"R1";"R_0603_1608Metric";1;"1k";;;
14;"C2,C5,C10,C7";"CP_Elec_3x5.3";4;"100nF";;;
15;"C4,C9";"CP_Elec_3x5.3";2;"10uF";;;
16;"U4";"WSON-6-1EP_2x2mm_P0.65mm_EP1x1.6mm_ThermalVias";1;"LP5912-2.5DRV";;;
17;"TP4";"TestPoint_Pad_D1.0mm";1;"TestPointIOPwr";;;
18;"D1";"LED_0603_1608Metric";1;"LED";;;
19;"TP3";"TestPoint_Pad_D1.0mm";1;"TestPointGnd";;;
20;"U1";"ZIF-441_Aries";1;"EMBER Macro";;;
21;"U2";"WSON-6-1EP_2x2mm_P0.65mm_EP1x1.6mm_ThermalVias";1;"LP5912-0.9DRV";;;
22;"SW3";"SW_DIP_SPSTx02_Slide_Omron_A6S-210x_W8.9mm_P2.54mm";1;"SW_DIP_x02";;;
23;"U3";"WSON-6-1EP_2x2mm_P0.65mm_EP1x1.6mm_ThermalVias";1;"LP5912-1.1DRV";;;

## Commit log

2022-12-09 6 layer
2022-12-10 12 layer board power routing done
2022-12-14 Getting more in shape
2022-12-14 Clean up
2022-12-15 Refactor and clean
2022-12-15 Add README
2022-12-15 Add gitignore
2022-12-15 Update schematic-checklist-lupton.md
    Initial comments. Need to re-examine macro pin labels & how they map to sockets.
2022-12-15 Fixes
2022-12-16 Save me
2022-12-16 20/160 tracks complete
2022-12-16 Finished routing one layer!
2022-12-16 Fix first layer DRC violations
2022-12-16 Last check on layer 1
2022-12-16 About 1/3 done with layer 2
2022-12-16 Close to halfway done with second layer
2022-12-16 More progress. 75% done overall
2022-12-16 More progress on routing layer 2 (about 2/3)
2022-12-16 Backup at 3/4
2022-12-16 About 90% done with layer 2
2022-12-16 Finished routing
2022-12-16 Fix DRC (before cleanup tracks/vias)
2022-12-16 Fix DRC using cleanup
2022-12-16 Fix DRC with cleanup (for real)
2022-12-16 DRC/LVS clean
2022-12-18 Minor fixes to signal lengths
2022-12-18 Update gitignore
2022-12-18 Commit PCB XML
2022-12-18 Add schematic BOM
2022-12-18 Add IPC file from Sierra Circuits stackup designer
2022-12-19 12 layer board final
2022-12-19 Add DFM report from Bay Area Circuits
2022-12-19 Updating schematic checklist
2022-12-19 Update checklists
2022-12-19 Add license
2022-12-19 Update TODO
2022-12-19 Update wishlist
